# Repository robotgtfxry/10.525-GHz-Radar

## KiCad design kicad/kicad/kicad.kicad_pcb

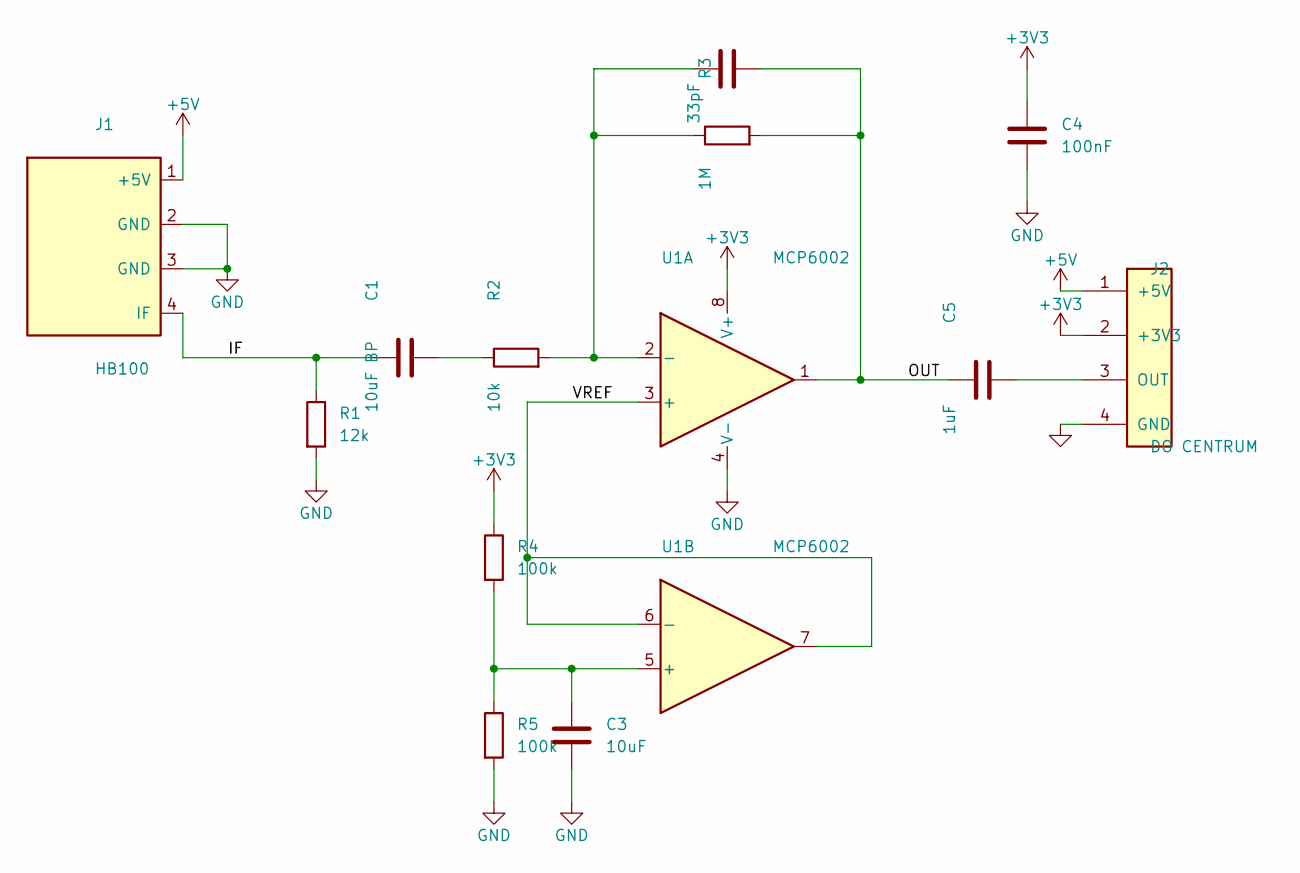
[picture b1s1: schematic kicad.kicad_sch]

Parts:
C1: 10uF BP; C_1210_3225Metric_Pad1.33x2.70mm_HandSolder
C2: 33pF; C_1206_3216Metric_Pad1.33x1.80mm_HandSolder
C3: 10uF; C_1210_3225Metric_Pad1.33x2.70mm_HandSolder
C4: 100nF; C_1206_3216Metric_Pad1.33x1.80mm_HandSolder
C5: 1uF; C_1206_3216Metric_Pad1.33x1.80mm_HandSolder
J1: HB100; HB100_Pads_4x_THT
J2: DO CENTRUM; JST_XH_B4B-XH-A_1x04_P2.50mm_Vertical
R1: 12k; R_1206_3216Metric_Pad1.30x1.75mm_HandSolder
R2: 10k; R_1206_3216Metric_Pad1.30x1.75mm_HandSolder
R3: 1M; R_1206_3216Metric_Pad1.30x1.75mm_HandSolder
R4, R5: 100k; R_1206_3216Metric_Pad1.30x1.75mm_HandSolder
U1: MCP6002; SOIC-8_3.9x4.9mm_P1.27mm

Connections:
+3V3: C4.1, J2.2 (+3V3), R4.1, U1.8 (V+)
+5V: J1.1 (+5V), J2.1 (+5V)
/IF: C1.1, J1.4 (IF), R1.1
/OUT: C2.2, C5.1, R3.2, U1.1
/VREF: U1.3 (+), U1.6 (-), U1.7
GND: C3.2, C4.2, J1.2 (GND), J1.3 (GND), J2.4 (GND), R1.2, R5.2, U1.4 (V-)
unnamed: C1.2, R2.1
unnamed: C5.2, J2.3 (OUT)
unnamed: C2.1, R2.2, R3.1, U1.2 (-)
unnamed: C3.1, R4.2, R5.1, U1.5 (+)

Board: 2 copper layers, 13 parts (0 on the bottom side), 10 nets, no tracks yet.

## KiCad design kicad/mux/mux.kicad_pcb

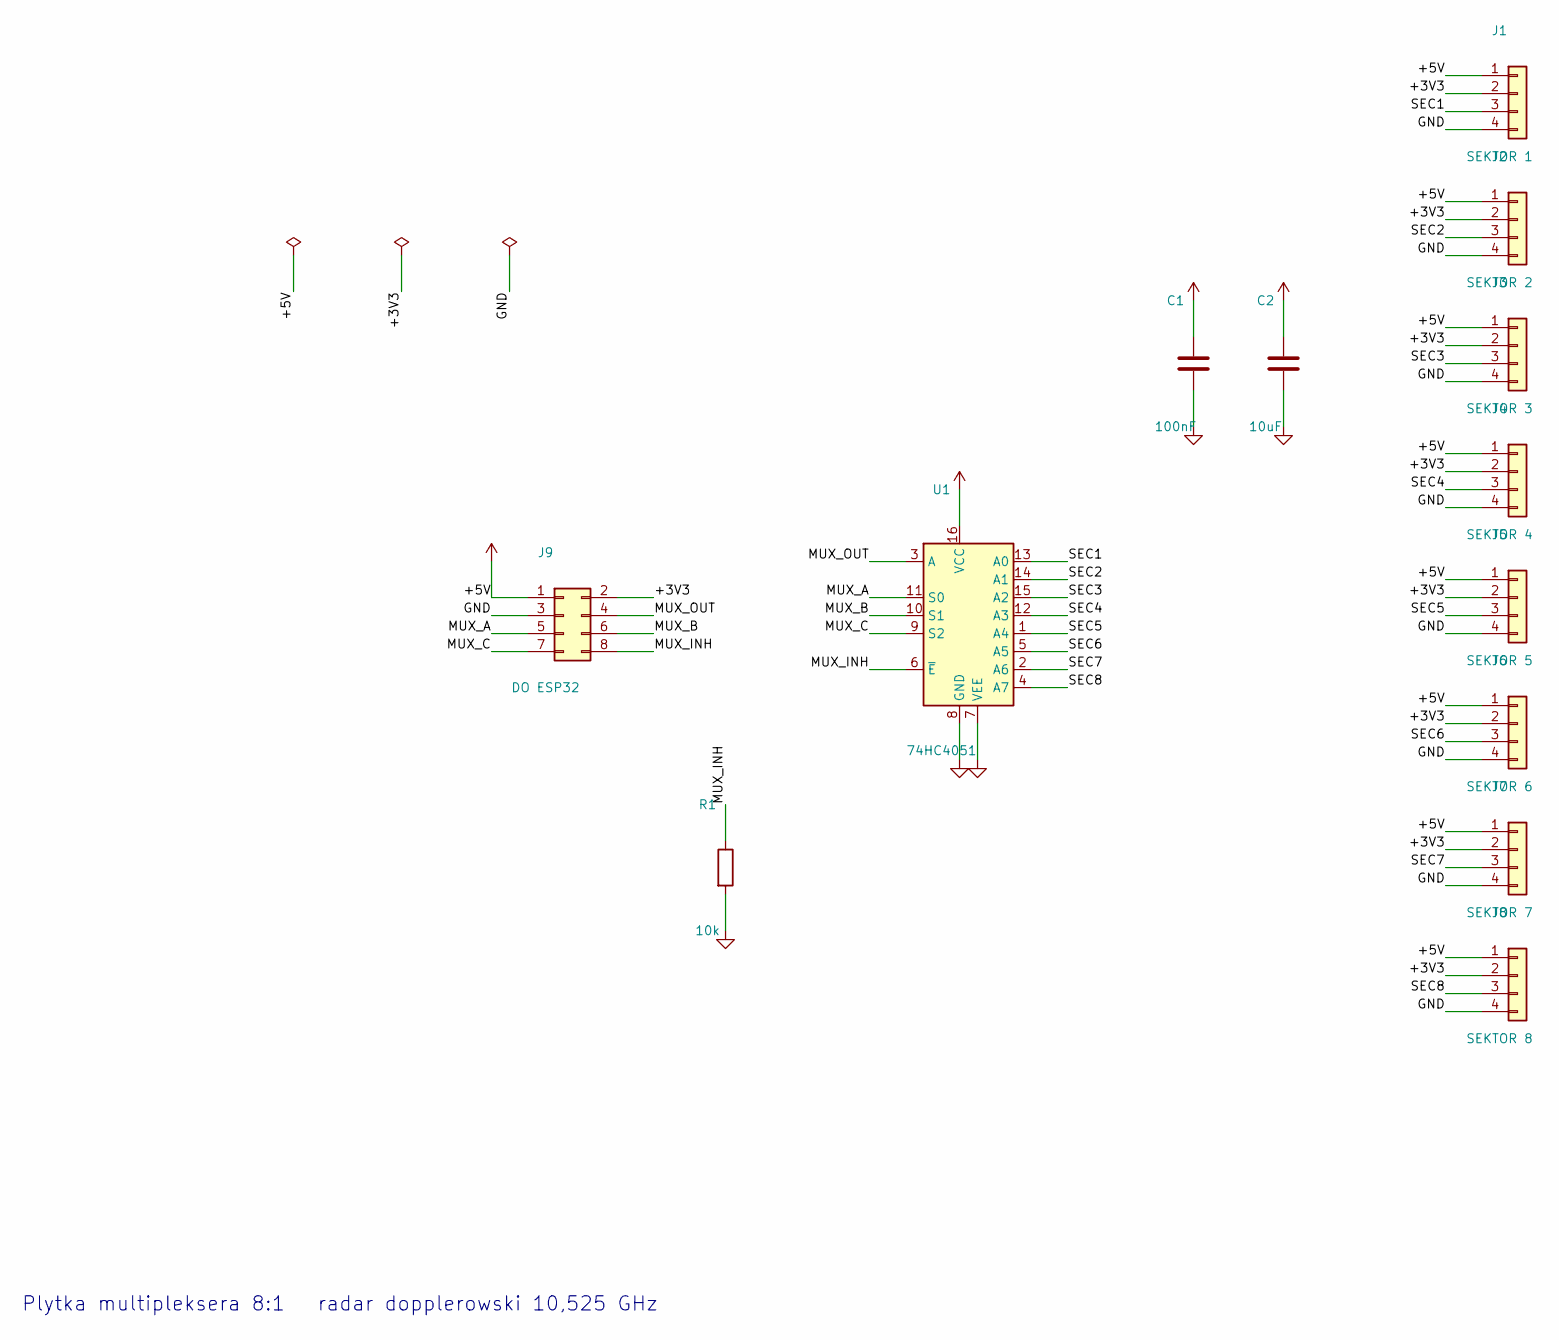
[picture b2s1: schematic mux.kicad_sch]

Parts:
C1: 100nF; C_1206_3216Metric_Pad1.33x1.80mm_HandSolder
C2: 10uF; C_1210_3225Metric_Pad1.33x2.70mm_HandSolder
J1: SEKTOR 1; JST_XH_B4B-XH-A_1x04_P2.50mm_Vertical
J2: SEKTOR 2; JST_XH_B4B-XH-A_1x04_P2.50mm_Vertical
J3: SEKTOR 3; JST_XH_B4B-XH-A_1x04_P2.50mm_Vertical
J4: SEKTOR 4; JST_XH_B4B-XH-A_1x04_P2.50mm_Vertical
J5: SEKTOR 5; JST_XH_B4B-XH-A_1x04_P2.50mm_Vertical
J6: SEKTOR 6; JST_XH_B4B-XH-A_1x04_P2.50mm_Vertical
J7: SEKTOR 7; JST_XH_B4B-XH-A_1x04_P2.50mm_Vertical
J8: SEKTOR 8; JST_XH_B4B-XH-A_1x04_P2.50mm_Vertical
J9: DO ESP32; PinHeader_2x04_P2.54mm_Vertical
R1: 10k; R_1206_3216Metric_Pad1.30x1.75mm_HandSolder
U1: 74HC4051; SOIC-16_3.9x9.9mm_P1.27mm

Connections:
+3V3: C1.1, C2.1, J1.2, J2.2, J3.2, J4.2, J5.2, J6.2, J7.2, J8.2, J9.2, U1.16 (VCC)
+5V: J1.1, J2.1, J3.1, J4.1, J5.1, J6.1, J7.1, J8.1, J9.1
/MUX_A: J9.5, U1.11 (S0)
/MUX_B: J9.6, U1.10 (S1)
/MUX_C: J9.7, U1.9 (S2)
/MUX_INH: J9.8, R1.1, U1.6 (~E)
/MUX_OUT: J9.4, U1.3 (A)
/SEC1: J1.3, U1.13 (A0)
/SEC2: J2.3, U1.14 (A1)
/SEC3: J3.3, U1.15 (A2)
/SEC4: J4.3, U1.12 (A3)
/SEC5: J5.3, U1.1 (A4)
/SEC6: J6.3, U1.5 (A5)
/SEC7: J7.3, U1.2 (A6)
/SEC8: J8.3, U1.4 (A7)
GND: C1.2, C2.2, J1.4, J2.4, J3.4, J4.4, J5.4, J6.4, J7.4, J8.4, J9.3, R1.2, U1.7 (VEE), U1.8 (GND)

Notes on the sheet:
Plytka multipleksera 8:1 radar dopplerowski 10,525 GHz

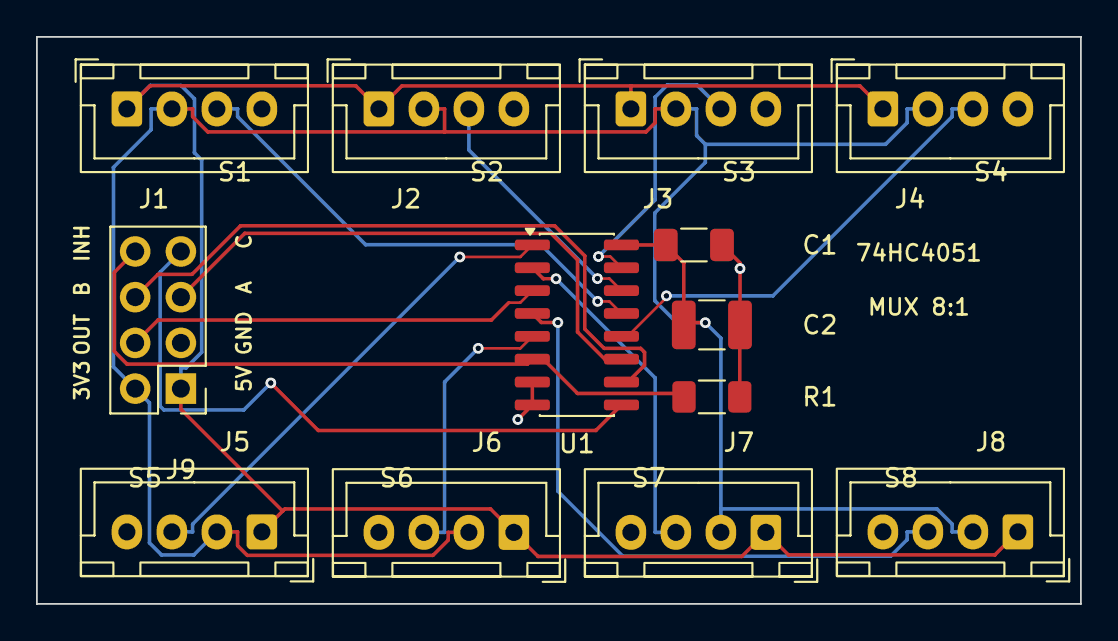
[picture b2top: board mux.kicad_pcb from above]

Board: 2 copper layers, 58.0 x 31.5 mm, 13 parts (0 on the bottom side), 16 nets.
